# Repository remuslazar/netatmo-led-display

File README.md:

Netatmo LED Display
===================

Project Goal
------------

Drive a 64x32 RGA LED Display and display current environmental data
from a Netatmo Weather-Station.

Technical Details
-----------------

The heart of the system is an
[Arduino Yún](http://arduino.cc/en/Main/ArduinoBoardYun?from=Products.ArduinoYUN).

The ATmega32u4 processor will drive the LCD-Display and the Atheros
Linux SOC will talk to the Netatmo API using the
[Netatmo Python Client](https://github.com/remuslazar/netatmo-python).

Using the 5x7 Font (included in the Adafruit GFX Library) the display
is capable of displaying 10x4 Chars (using some spacing between the
chars).

Project Status
--------------

Currently WIP and not fully functional (just displaying some static
demo).

Arduino
-------

This project uses the Adafruit_GXF libraries, which is available on
Github:

```
cd ~/Documents/Arduino/libraries/ # your Arduino libraries dir
git clone https://github.com/adafruit/Adafruit-GFX-Library.git
```

Initially the `Ultrathin LED Matrix Library` was considered (see the
Github-link below). But because of the bad performance and missing
features (green led was not implemented), the whole hardware related
stuff was rewritten from scratch and integrated in the `LEDDisplay`
library, which is bundled with this project (separate library, can be
used also for other projects as well).

Using the current implementation, the matrix refresh cycles (full
refresh running on 100Hz) do use only about 12% of the 16MHz CPU,
leaving enough room for the main application.

PCB / Eagle
-----------

A custom Arduino-shield is provided for the connection between the
Arduino and the LED Display. To minimize costs the shield is one-sided
(TOP coper).

References
----------

* [LDP-6432 LCD Matrix Display](http://www.embeddedadventures.com/led_matrix_display_LDP-6432.html)
* [ATmega32U4 Datasheet](http://www.atmel.com/Images/7766s.pdf)
* [Adafruit GFX Lib Tutorial](https://learn.adafruit.com/downloads/pdf/adafruit-gfx-graphics-library.pdf)
* [Adafruit GFX Arduino Library](https://github.com/adafruit/Adafruit-GFX-Library)
* [Ultrathin LED Matrix Library](https://github.com/Seeed-Studio/Ultrathin_LED_Matrix)
* [GLCD Library](https://github.com/andygock/glcd)

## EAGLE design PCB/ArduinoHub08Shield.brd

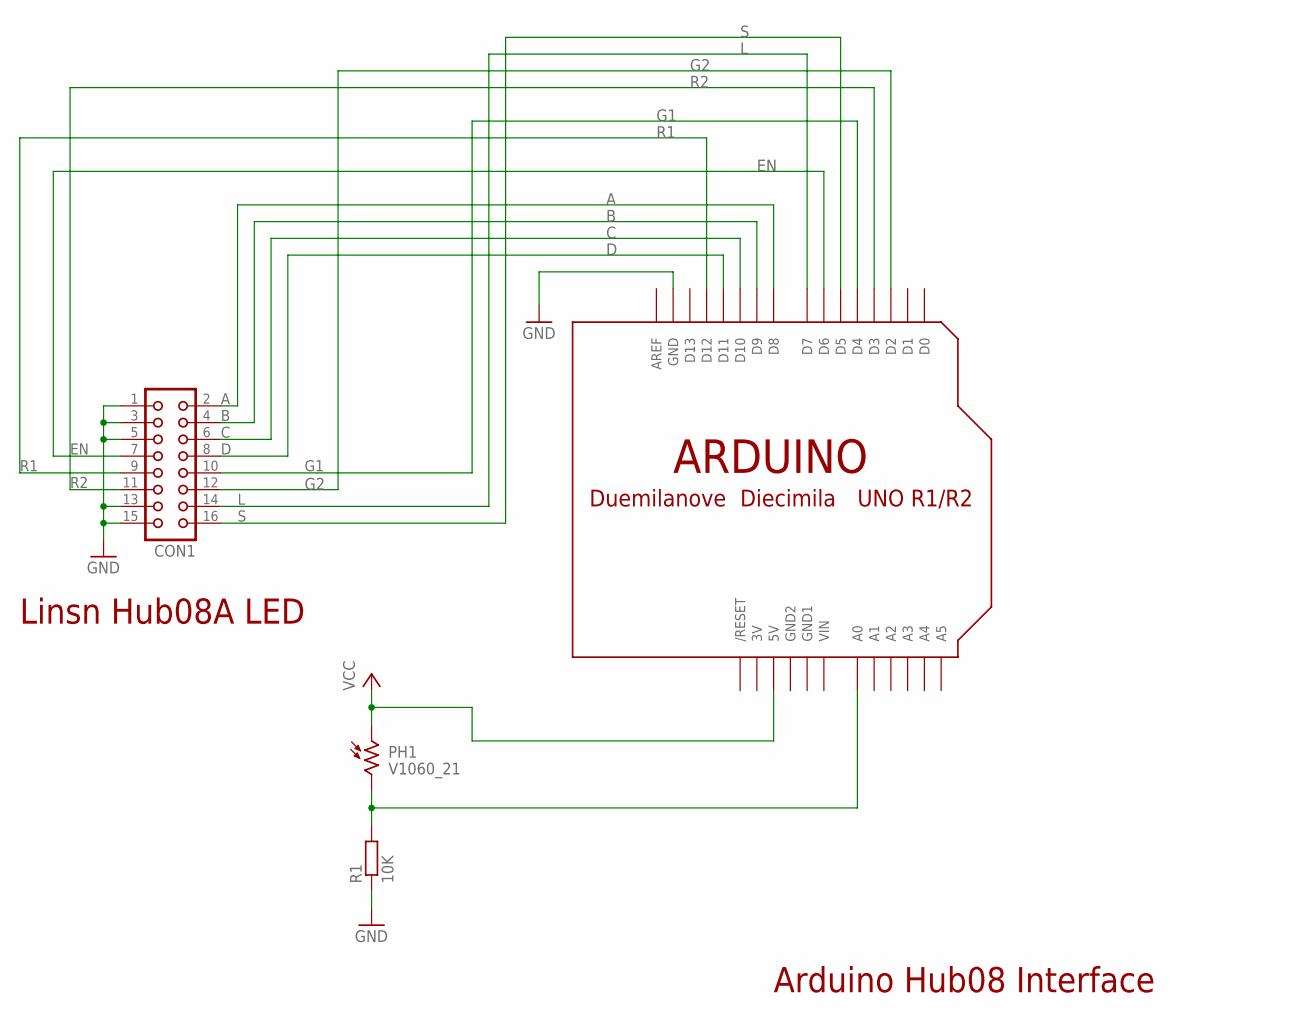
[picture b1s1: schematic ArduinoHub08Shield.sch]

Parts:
CON1: CON16
PH1: V1060_21; TO-5_V10
R1: 10K; 0204/7
U$1: ARDUINO-NOHOLE

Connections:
3V: U$1.3V
A: CON1.2, U$1.D8
B: CON1.4, U$1.D9
C: CON1.6, U$1.D10
D: CON1.8, U$1.D11
EN: CON1.7, U$1.D6
G1: CON1.10, U$1.D4
G2: CON1.12, U$1.D2
GND: CON1.1, CON1.3, CON1.5, CON1.13, CON1.15, R1.1, U$1.GND
GND1: U$1.GND1
GND2: U$1.GND2
L: CON1.14, U$1.D7
unnamed: PH1.2, R1.2, U$1.A0
R1: CON1.9, U$1.D12
R2: CON1.11, U$1.D3
S: CON1.16, U$1.D5
VCC: PH1.1, U$1.5V
VIN: U$1.VIN

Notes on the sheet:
Arduino Hub08 Interface
Linsn Hub08A LED

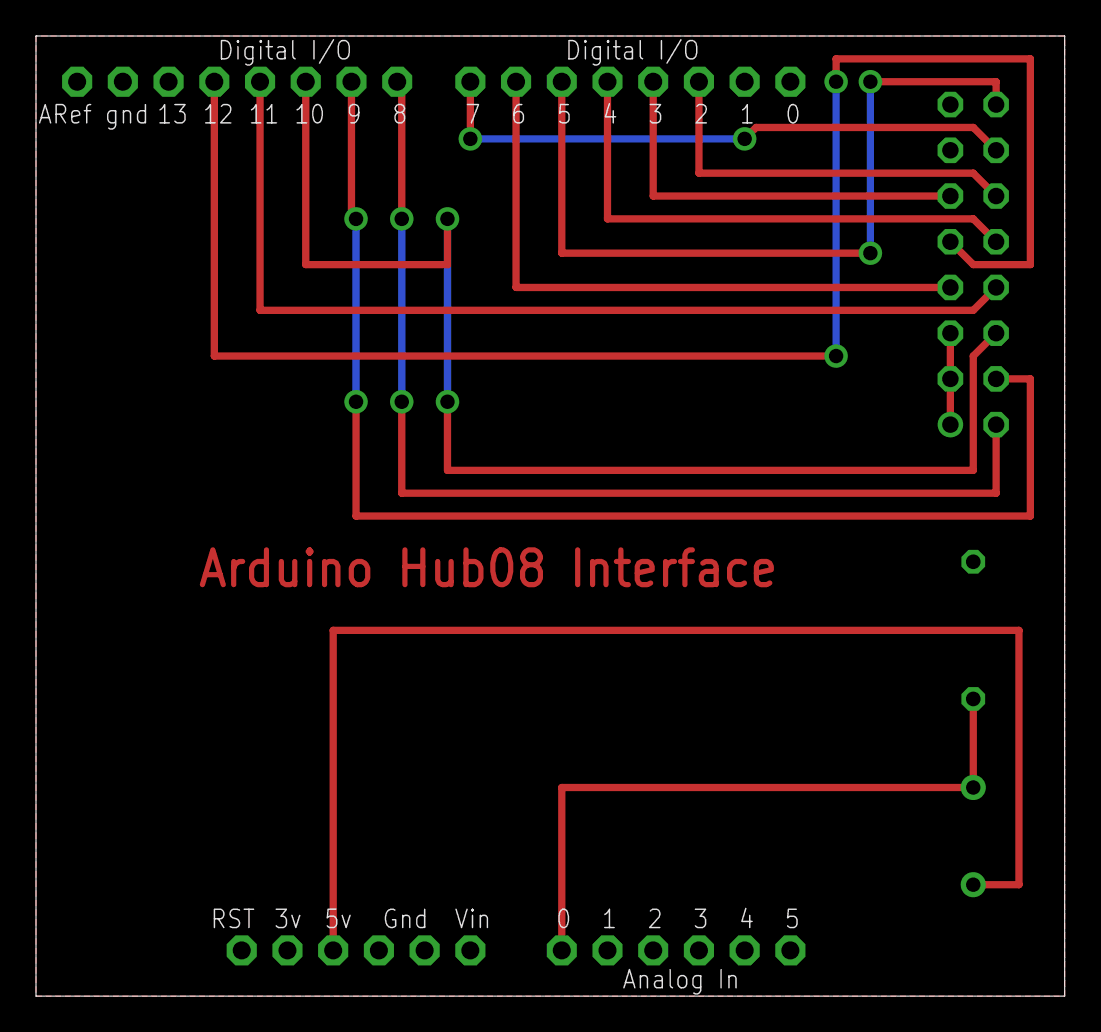
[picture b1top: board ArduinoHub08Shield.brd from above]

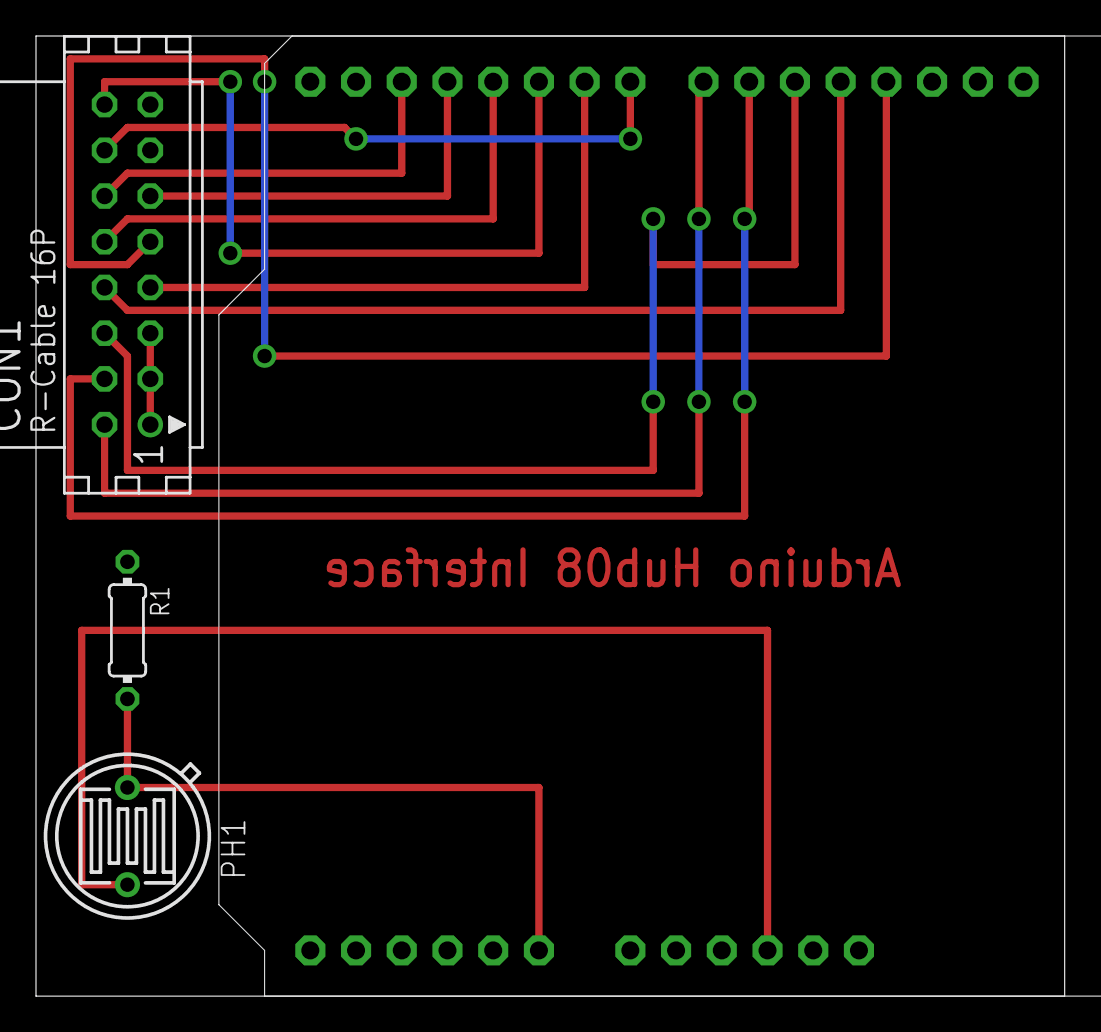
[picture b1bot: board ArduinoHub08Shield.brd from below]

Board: 2 copper layers, 57.1 x 53.3 mm, 4 parts (3 on the bottom side), 14 nets.

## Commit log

2015-01-25 profile max. refresh/s
    measure how many refresh cycles per second are posible using
    the current implementation (c-code).
2015-01-26 Refactoring of the LCDDisplay library
    because of the bad performance of the Ultrathin LED_Matrix
    library (only about 25 frames/s refresh rate..) the complete
    LEDDisplay Library has to be redesigned to talk directly to the
    hardware in a more efficient way.
2015-01-26 ISR implemented, profile the current refresh rate
2015-01-26 isr refactored and fully implemented (tests pending..)
2015-01-26 remote the debug switched
2015-01-27 another refactoring and code cleanups, see commit msg.
    For performance reasons we constraint the usage of the
    hardware ports to allow us to be more performant in the
    inner loop of the ISR.
    The schematic and PCM were changed to adapt these constraints.
2015-01-27 minor refactoring: use the constants for the available colors and not integers
2015-01-27 be more robust if the row variable go out of bounds for some reason
2015-01-27 indending..
2015-01-27 setup the clock signal pin as output
    plus some cosmetic stuff
2015-01-27 refactoring: use a struct for the display data
2015-01-27 bugfix: data lines are inverted
2015-01-27 use the _BV() macro instead of the hex literals
2015-01-27 ATmega32U4 datasheet included
2015-01-27 minor refactoring of the ISR to get more accurate timings
2015-01-27 playing with TIMER3
2015-01-27 bugfix: fixed an ugly bug in drawPixel()
    The calculation of the segment was wrong
2015-01-27 dumpScreen() method
    a handy debugging method to dump the current content of the frame
    buffer to the serial console.
2015-01-27 some cleanups in the main routine
2015-01-27 boundary check in drawPixel()
2015-01-27 minor tweaks in the demo view
2015-01-28 some tweaks in dumpScreen()
    show a nicer frame arround the screen
2015-01-28 demo screen update
2015-01-30 Arduino <> hub08 pin mapping
2015-01-30 fix: G1 arduino pin was wrong
2015-01-31 bugfix: output mode for all pins was not setup correctly
    The portModeRegister macro was not used correctly.
    Now the direction register is also hardcoded and the
    code setting up the port direction was refactored.
2015-01-31 minor refactoring of Hardware.h
    dont save the mask directly, use some static macros for that
2015-01-31 do the init of the row, buffptr in the begin() method
2015-01-31 inline doc
2015-01-31 refactoring of the ISR/timer interoperability
    use the same timer for ISR and PWM (for brightness control).
    See inline documentation for details.
2015-01-31 debug settings reviewed
2015-02-02 pwm is not working right now
2015-02-02 this should fix the pwm bug (to be tested..)
2015-02-02 Create gh-pages branch via GitHub
2015-02-02 add prototype image
2015-02-02 prototype image in the README.md
2015-02-04 double buffering implemented
2015-02-04 timer4 setup was buggy
    Because of the missing _BV() wrap the timer4 setup was buggy.
    The cie correction for the brightness was removed, maybe this can
    be re-enabled again in the future, if needed..
2015-02-04 bugfix in dumpScreen(): was not using the front buffer
2015-02-04 some tweaks for the demo-display
    using bigger font, spacing getuned..
2015-02-06 set the display brightness to 50%
2015-02-06 first working release on yun
    - hardware wiring tweaks (on yun pins 0,1 are not available)
    - use the bridge library to access the data from Netatmo
    - display live data
2015-02-09 Hardware Update (Schematic/PCB and Hardware.h)
    Because we cant use the digital pins 0,1 on Yun, we updated
    the schematic and layout to use different pins.
    Now the A-D address lines are also on the high nibble of
    PORTB, which leave some room for even more tuning of the
    ISR.
2015-02-10 #define YUN added
    Sometimes for debugging it is useful to test the codebase on a
    e.g. Arduino Leonardo and disable the Bridge code alltogether.
2015-02-10 playing with the LDR
2015-02-10 arduino main sketch file refactored
    basically only cosmetic stuff (variables renamed, better comments, ..)
2015-02-10 better algo for the process* functions in the main sketch file
2015-02-10 PCB/schematic update: LDR light sensor added
2015-02-10 deleted onbsolete pcb png file
